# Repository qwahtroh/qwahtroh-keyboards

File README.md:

# qwahtroh-keyboards
my keyboard projects

usually inspired by a cool keyboard on r/mk that wasn't hotswap or ortholinear

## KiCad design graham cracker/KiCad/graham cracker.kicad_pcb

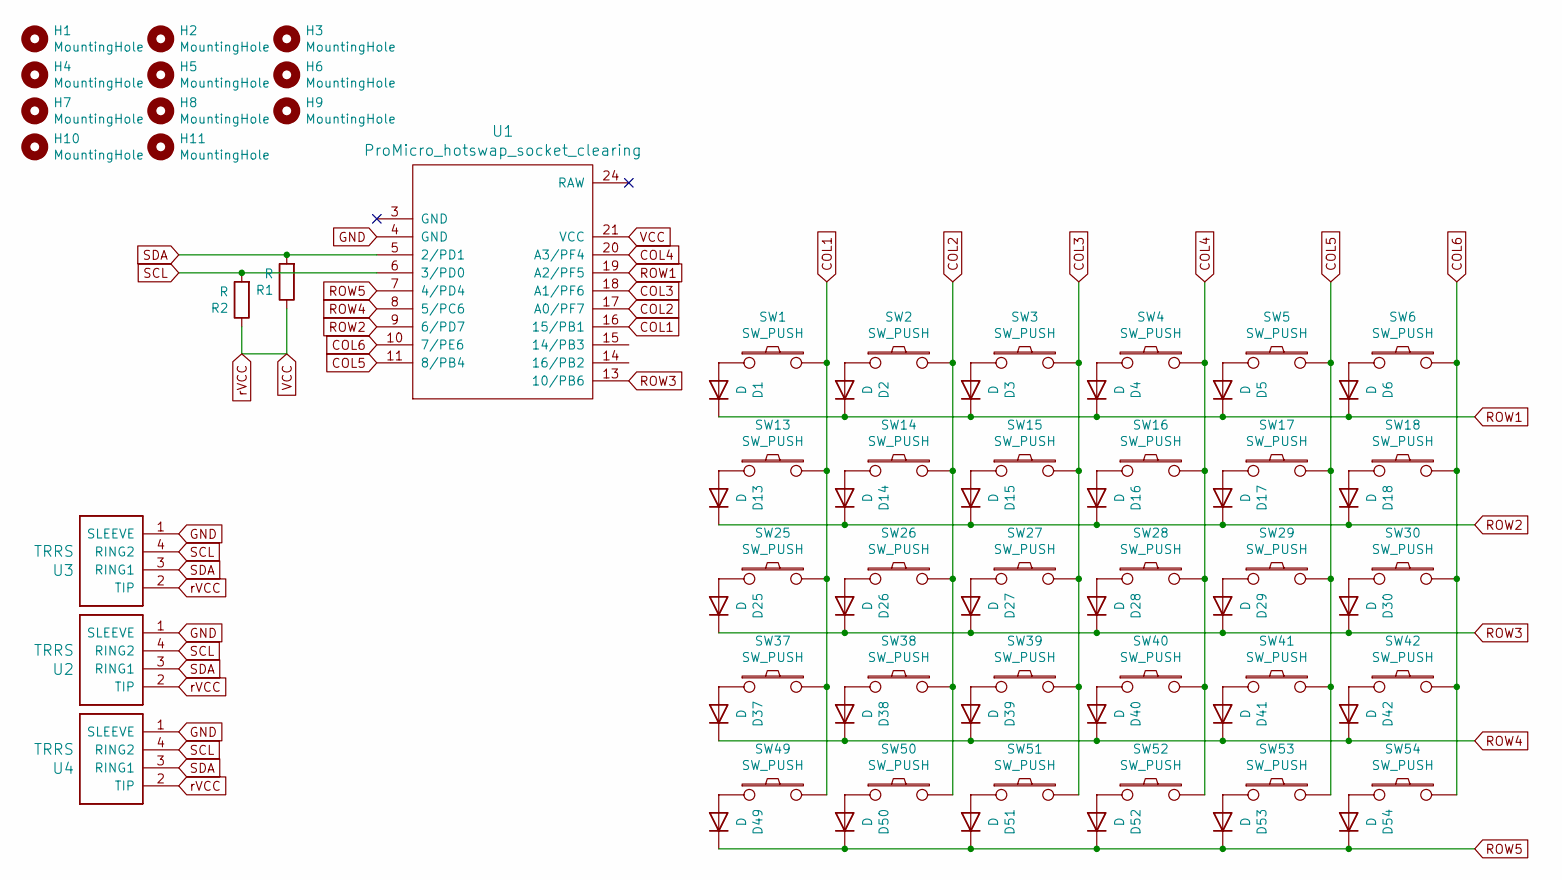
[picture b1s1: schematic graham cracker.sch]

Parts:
D1, D2, D3, D4, D5, D6, D13, D14, D15, D16, D17, D18, D25, D26, D27, D28, D29, D30, D37, D38, D39, D40, D41, D42, D49, D50, D51, D52, D53, D54: D; D_SOD123F
H1, H2, H3, H4, H5, H6, H7, H8, H9, H10, H11: MountingHole; HOLE_M3
R1, R2: R; R_Axial_DIN0207_L6.3mm_D2.5mm_P10.16mm_Horizontal
SW1, SW2, SW3, SW4, SW5, SW6, SW13, SW14, SW15, SW16, SW17, SW18, SW25, SW26, SW27, SW28, SW29, SW30, SW37, SW38, SW39, SW40, SW41, SW42, SW49, SW50, SW51, SW52, SW53, SW54: SW_PUSH; Kailh_MX_Socket
U1: ProMicro_hotswap_socket_clearing; ArduinoProMicro_hotswap_socket_clear
U2, U3, U4: TRRS; TRRS-PJ-320A

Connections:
COL1: SW1.2, SW13.2, SW25.2, SW37.2, SW49.2, U1.16 (15/PB1)
COL2: SW2.2, SW14.2, SW26.2, SW38.2, SW50.2, U1.17 (A0/PF7)
COL3: SW3.2, SW15.2, SW27.2, SW39.2, SW51.2, U1.18 (A1/PF6)
COL4: SW4.2, SW16.2, SW28.2, SW40.2, SW52.2, U1.20 (A3/PF4)
COL5: SW5.2, SW17.2, SW29.2, SW41.2, SW53.2, U1.11 (8/PB4)
COL6: SW6.2, SW18.2, SW30.2, SW42.2, SW54.2, U1.10 (7/PE6)
GND: U1.4 (GND), U2.1 (SLEEVE), U3.1 (SLEEVE), U4.1 (SLEEVE)
unnamed: D1.2 (A), SW1.1
unnamed: D2.2 (A), SW2.1
unnamed: D3.2 (A), SW3.1
unnamed: D4.2 (A), SW4.1
unnamed: D5.2 (A), SW5.1
unnamed: D6.2 (A), SW6.1
unnamed: D13.2 (A), SW13.1
unnamed: D14.2 (A), SW14.1
unnamed: D15.2 (A), SW15.1
unnamed: D16.2 (A), SW16.1
unnamed: D17.2 (A), SW17.1
unnamed: D18.2 (A), SW18.1
unnamed: D25.2 (A), SW25.1
unnamed: D26.2 (A), SW26.1
unnamed: D27.2 (A), SW27.1
unnamed: D28.2 (A), SW28.1
unnamed: D29.2 (A), SW29.1
unnamed: D30.2 (A), SW30.1
unnamed: D37.2 (A), SW37.1
unnamed: D38.2 (A), SW38.1
unnamed: D39.2 (A), SW39.1
unnamed: D40.2 (A), SW40.1
unnamed: D41.2 (A), SW41.1
unnamed: D42.2 (A), SW42.1
unnamed: D49.2 (A), SW49.1
unnamed: D50.2 (A), SW50.1
unnamed: D51.2 (A), SW51.1
unnamed: D52.2 (A), SW52.1
unnamed: D53.2 (A), SW53.1
unnamed: D54.2 (A), SW54.1
ROW1: D1.1 (K), D2.1 (K), D3.1 (K), D4.1 (K), D5.1 (K), D6.1 (K), U1.19 (A2/PF5)
ROW2: D13.1 (K), D14.1 (K), D15.1 (K), D16.1 (K), D17.1 (K), D18.1 (K), U1.9 (6/PD7)
ROW3: D25.1 (K), D26.1 (K), D27.1 (K), D28.1 (K), D29.1 (K), D30.1 (K), U1.13 (10/PB6)
ROW4: D37.1 (K), D38.1 (K), D39.1 (K), D40.1 (K), D41.1 (K), D42.1 (K), U1.8 (5/PC6)
ROW5: D49.1 (K), D50.1 (K), D51.1 (K), D52.1 (K), D53.1 (K), D54.1 (K), U1.7 (4/PD4)
SCL: R2.2, U1.6 (3/PD0), U2.4 (RING2), U3.4 (RING2), U4.4 (RING2)
SDA: R1.2, U1.5 (2/PD1), U2.3 (RING1), U3.3 (RING1), U4.3 (RING1)
VCC: R1.1, R2.1, U1.21 (VCC), U2.2 (TIP), U3.2 (TIP), U4.2 (TIP)

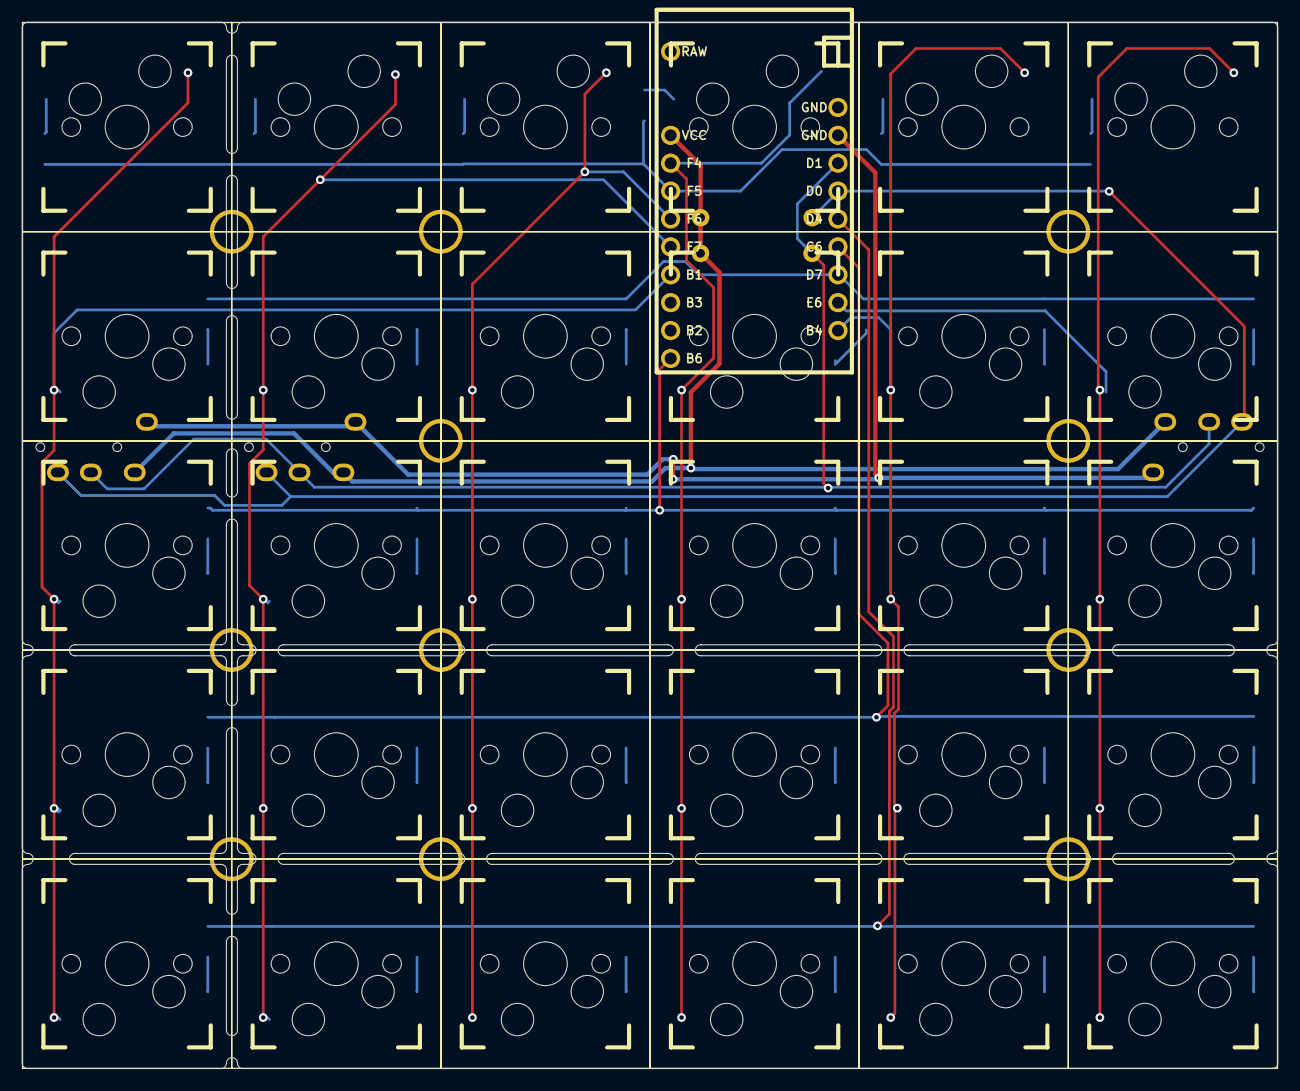
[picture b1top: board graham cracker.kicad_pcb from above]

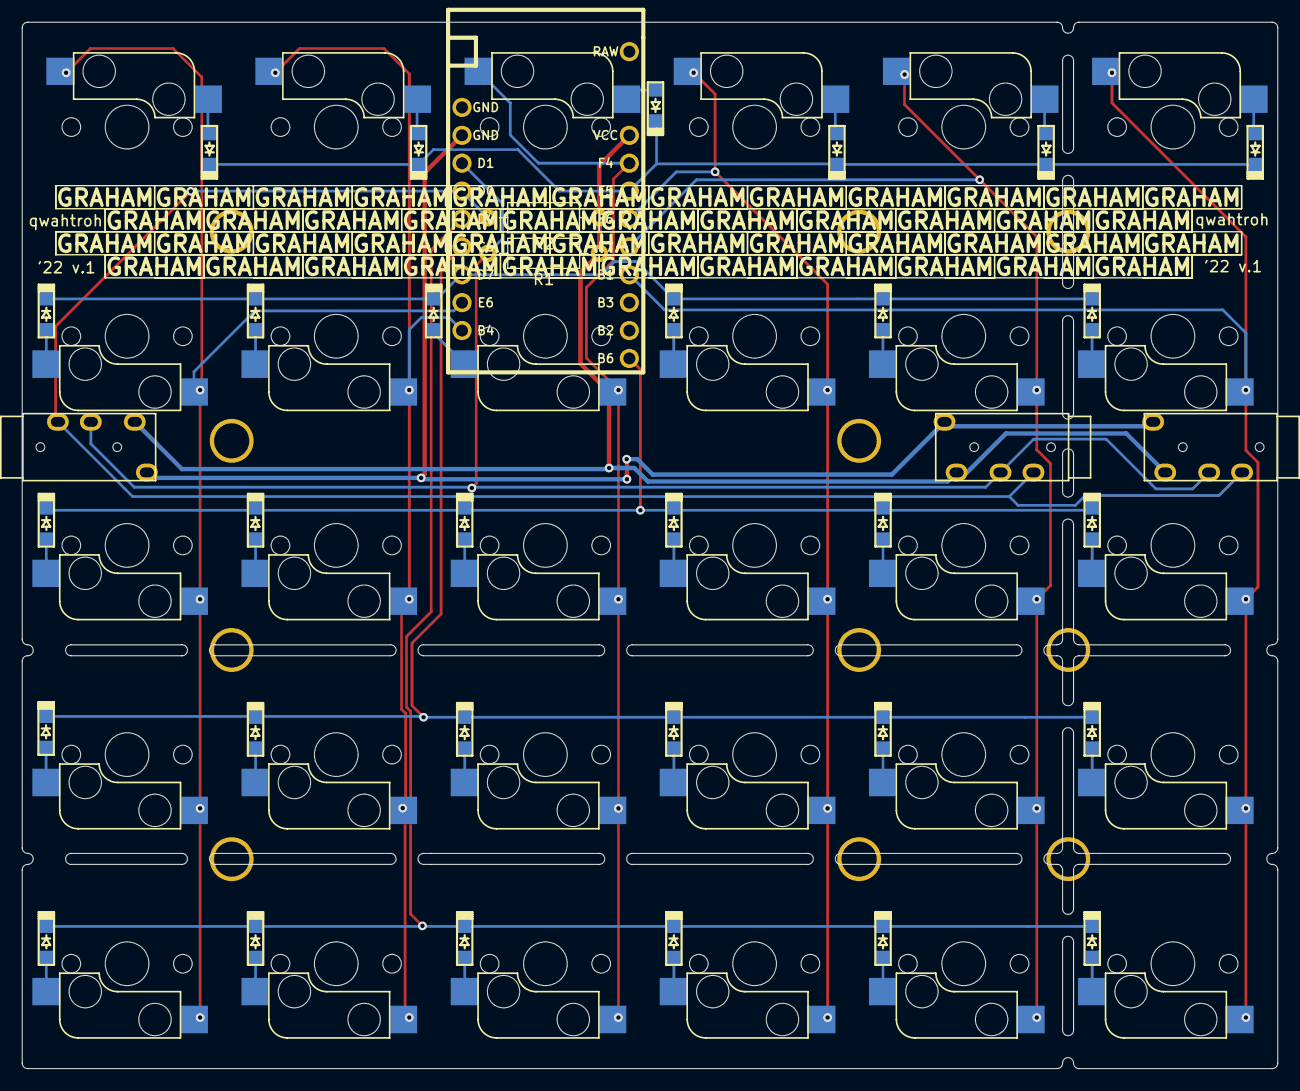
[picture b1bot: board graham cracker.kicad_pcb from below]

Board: 2 copper layers, 114.3 x 95.3 mm, 77 parts (36 on the bottom side), 45 nets.

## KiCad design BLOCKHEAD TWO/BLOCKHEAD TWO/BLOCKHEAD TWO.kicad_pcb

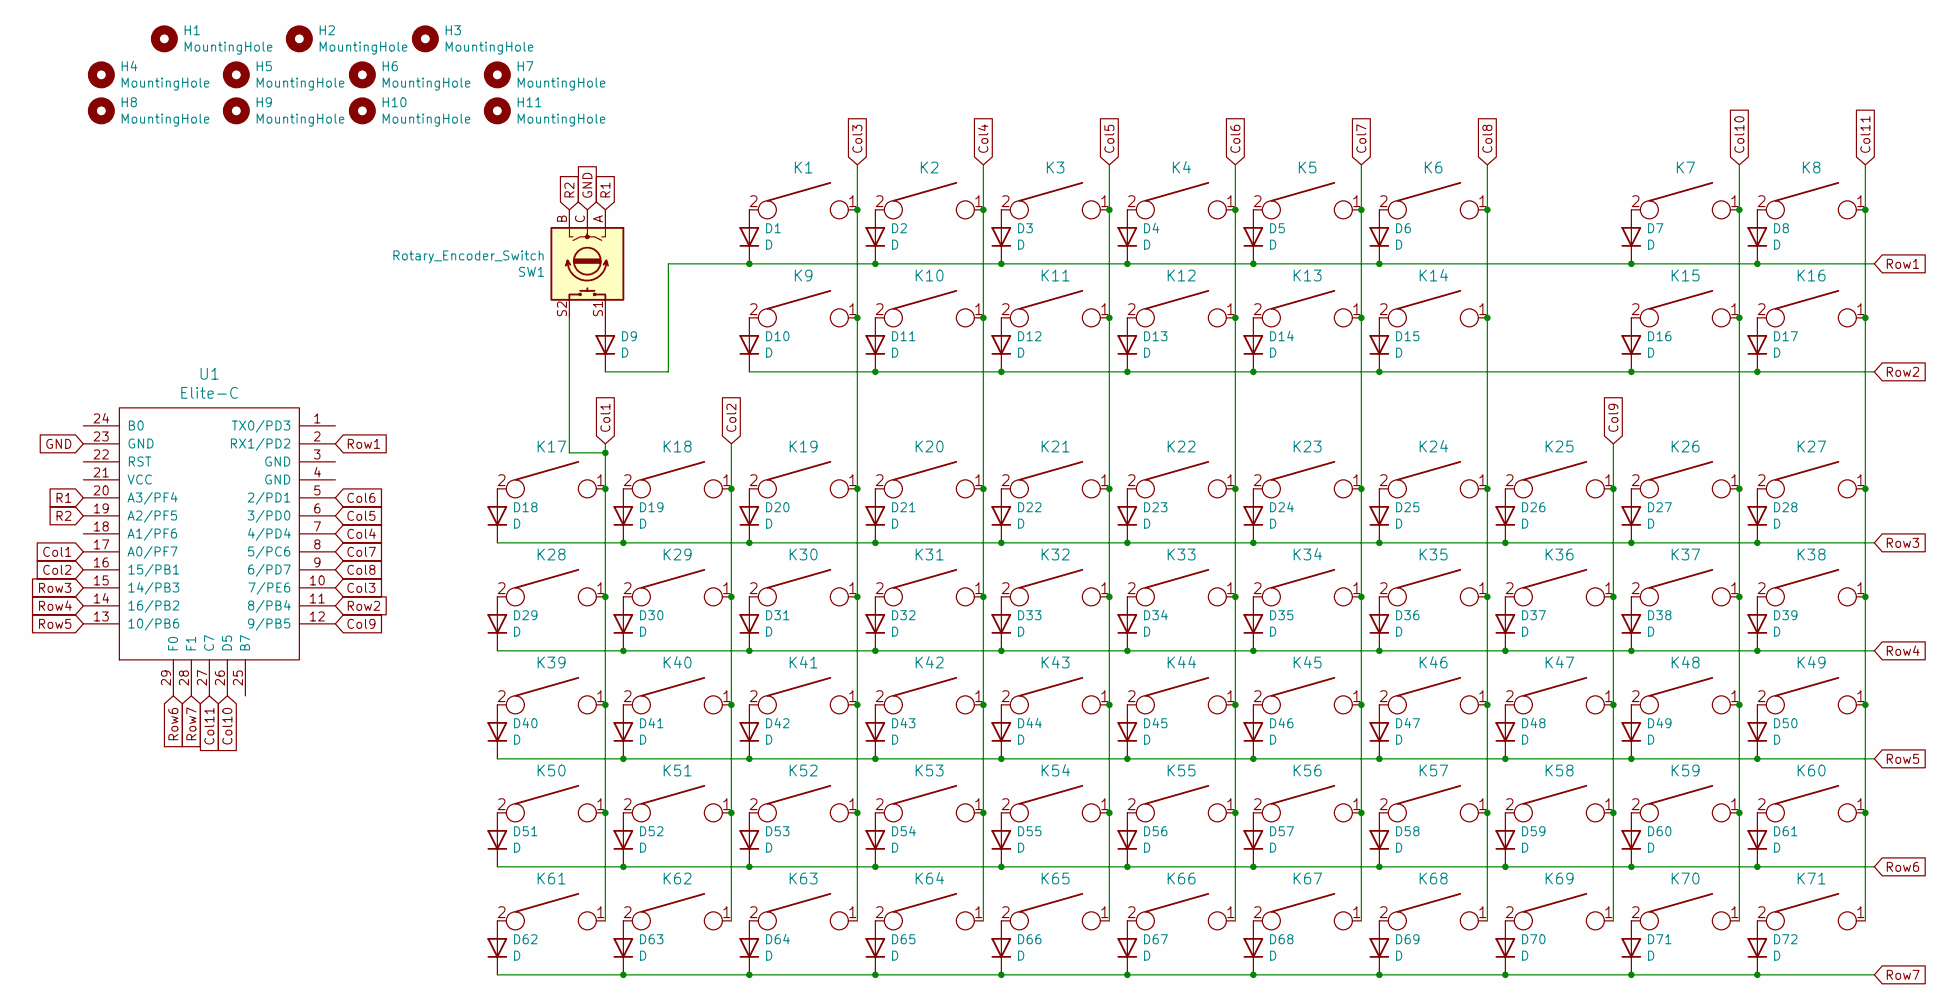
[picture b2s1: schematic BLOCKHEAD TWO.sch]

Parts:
D1, D2, D3, D4, D5, D6, D7, D8, D9, D10, D11, D12, D13, D14, D15, D16, D17, D18, D19, D20, D21, D22, D23, D24, D25, D26, D27, D28, D29, D30, D31, D32, D33, D34, D35, D36, D37, D38, D39, D40, D41, D42, D43, D44, D45, D46, D47, D48, D49, D50, D51, D52, D53, D54, D55, D56, D57, D58, D59, D60, D61, D62, D63, D64, D65, D66, D67, D68, D69, D70, D71, D72: D; D_SOD123F
H1, H2, H3, H4, H5, H6, H7, H8, H9, H10, H11: MountingHole; HOLE_M3
K1, K2, K3, K4, K5, K6, K7, K8, K9, K10, K11, K12, K13, K14, K15, K16, K17, K18, K19, K20, K21, K22, K23, K24, K25, K26, K27, K28, K29, K30, K31, K32, K33, K34, K35, K36, K37, K38, K39, K40, K41, K42, K43, K44, K45, K46, K47, K48, K49, K50, K51, K52, K53, K54, K55, K56, K57, K58, K59, K60, K61, K62, K63, K64, K65, K66, K67, K68, K69, K70, K71: KEYSW; Kailh_MX_Socket
SW1: Rotary_Encoder_Switch; RotaryEncoder_EC11
U1: Elite-C

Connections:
Col1: K17.1, K28.1, K39.1, K50.1, K61.1, SW1.S2, U1.17 (A0/PF7)
Col2: K18.1, K29.1, K40.1, K51.1, K62.1, U1.16 (15/PB1)
Col3: K1.1, K9.1, K19.1, K30.1, K41.1, K52.1, K63.1, U1.10 (7/PE6)
Col4: K2.1, K10.1, K20.1, K31.1, K42.1, K53.1, K64.1, U1.7 (4/PD4)
Col5: K3.1, K11.1, K21.1, K32.1, K43.1, K54.1, K65.1, U1.6 (3/PD0)
Col6: K4.1, K12.1, K22.1, K33.1, K44.1, K55.1, K66.1, U1.5 (2/PD1)
Col7: K5.1, K13.1, K23.1, K34.1, K45.1, K56.1, K67.1, U1.8 (5/PC6)
Col8: K6.1, K14.1, K24.1, K35.1, K46.1, K57.1, K68.1, U1.9 (6/PD7)
Col9: K25.1, K36.1, K47.1, K58.1, K69.1, U1.12 (9/PB5)
Col10: K7.1, K15.1, K26.1, K37.1, K48.1, K59.1, K70.1, U1.26 (D5)
Col11: K8.1, K16.1, K27.1, K38.1, K49.1, K60.1, K71.1, U1.27 (C7)
GND: SW1.C, U1.23 (GND)
unnamed: D1.2 (A), K1.2
unnamed: D2.2 (A), K2.2
unnamed: D3.2 (A), K3.2
unnamed: D4.2 (A), K4.2
unnamed: D5.2 (A), K5.2
unnamed: D6.2 (A), K6.2
unnamed: D7.2 (A), K7.2
unnamed: D8.2 (A), K8.2
unnamed: D9.2 (A), SW1.S1
unnamed: D10.2 (A), K9.2
unnamed: D11.2 (A), K10.2
unnamed: D12.2 (A), K11.2
unnamed: D13.2 (A), K12.2
unnamed: D14.2 (A), K13.2
unnamed: D15.2 (A), K14.2
unnamed: D16.2 (A), K15.2
unnamed: D17.2 (A), K16.2
unnamed: D18.2 (A), K17.2
unnamed: D19.2 (A), K18.2
unnamed: D20.2 (A), K19.2
unnamed: D21.2 (A), K20.2
unnamed: D22.2 (A), K21.2
unnamed: D23.2 (A), K22.2
unnamed: D24.2 (A), K23.2
unnamed: D25.2 (A), K24.2
unnamed: D26.2 (A), K25.2
unnamed: D27.2 (A), K26.2
unnamed: D28.2 (A), K27.2
unnamed: D29.2 (A), K28.2
unnamed: D30.2 (A), K29.2
unnamed: D31.2 (A), K30.2
unnamed: D32.2 (A), K31.2
unnamed: D33.2 (A), K32.2
unnamed: D34.2 (A), K33.2
unnamed: D35.2 (A), K34.2
unnamed: D36.2 (A), K35.2
unnamed: D37.2 (A), K36.2
unnamed: D38.2 (A), K37.2
unnamed: D39.2 (A), K38.2
unnamed: D40.2 (A), K39.2
unnamed: D41.2 (A), K40.2
unnamed: D42.2 (A), K41.2
unnamed: D43.2 (A), K42.2
unnamed: D44.2 (A), K43.2
unnamed: D45.2 (A), K44.2
unnamed: D46.2 (A), K45.2
unnamed: D47.2 (A), K46.2
unnamed: D48.2 (A), K47.2
unnamed: D49.2 (A), K48.2
unnamed: D50.2 (A), K49.2
unnamed: D51.2 (A), K50.2
unnamed: D52.2 (A), K51.2
unnamed: D53.2 (A), K52.2
unnamed: D54.2 (A), K53.2
unnamed: D55.2 (A), K54.2
unnamed: D56.2 (A), K55.2
unnamed: D57.2 (A), K56.2
unnamed: D58.2 (A), K57.2
unnamed: D59.2 (A), K58.2
unnamed: D60.2 (A), K59.2
unnamed: D61.2 (A), K60.2
unnamed: D62.2 (A), K61.2
unnamed: D63.2 (A), K62.2
unnamed: D64.2 (A), K63.2
unnamed: D65.2 (A), K64.2
unnamed: D66.2 (A), K65.2
unnamed: D67.2 (A), K66.2
unnamed: D68.2 (A), K67.2
unnamed: D69.2 (A), K68.2
unnamed: D70.2 (A), K69.2
unnamed: D71.2 (A), K70.2
unnamed: D72.2 (A), K71.2
R1: SW1.A, U1.20 (A3/PF4)
R2: SW1.B, U1.19 (A2/PF5)
Row1: D1.1 (K), D2.1 (K), D3.1 (K), D4.1 (K), D5.1 (K), D6.1 (K), D7.1 (K), D8.1 (K), D9.1 (K), U1.2 (RX1/PD2)
Row2: D10.1 (K), D11.1 (K), D12.1 (K), D13.1 (K), D14.1 (K), D15.1 (K), D16.1 (K), D17.1 (K), U1.11 (8/PB4)
Row3: D18.1 (K), D19.1 (K), D20.1 (K), D21.1 (K), D22.1 (K), D23.1 (K), D24.1 (K), D25.1 (K), D26.1 (K), D27.1 (K), D28.1 (K), U1.15 (14/PB3)
Row4: D29.1 (K), D30.1 (K), D31.1 (K), D32.1 (K), D33.1 (K), D34.1 (K), D35.1 (K), D36.1 (K), D37.1 (K), D38.1 (K), D39.1 (K), U1.14 (16/PB2)
Row5: D40.1 (K), D41.1 (K), D42.1 (K), D43.1 (K), D44.1 (K), D45.1 (K), D46.1 (K), D47.1 (K), D48.1 (K), D49.1 (K), D50.1 (K), U1.13 (10/PB6)
Row6: D51.1 (K), D52.1 (K), D53.1 (K), D54.1 (K), D55.1 (K), D56.1 (K), D57.1 (K), D58.1 (K), D59.1 (K), D60.1 (K), D61.1 (K), U1.29 (F0)
Row7: D62.1 (K), D63.1 (K), D64.1 (K), D65.1 (K), D66.1 (K), D67.1 (K), D68.1 (K), D69.1 (K), D70.1 (K), D71.1 (K), D72.1 (K), U1.28 (F1)

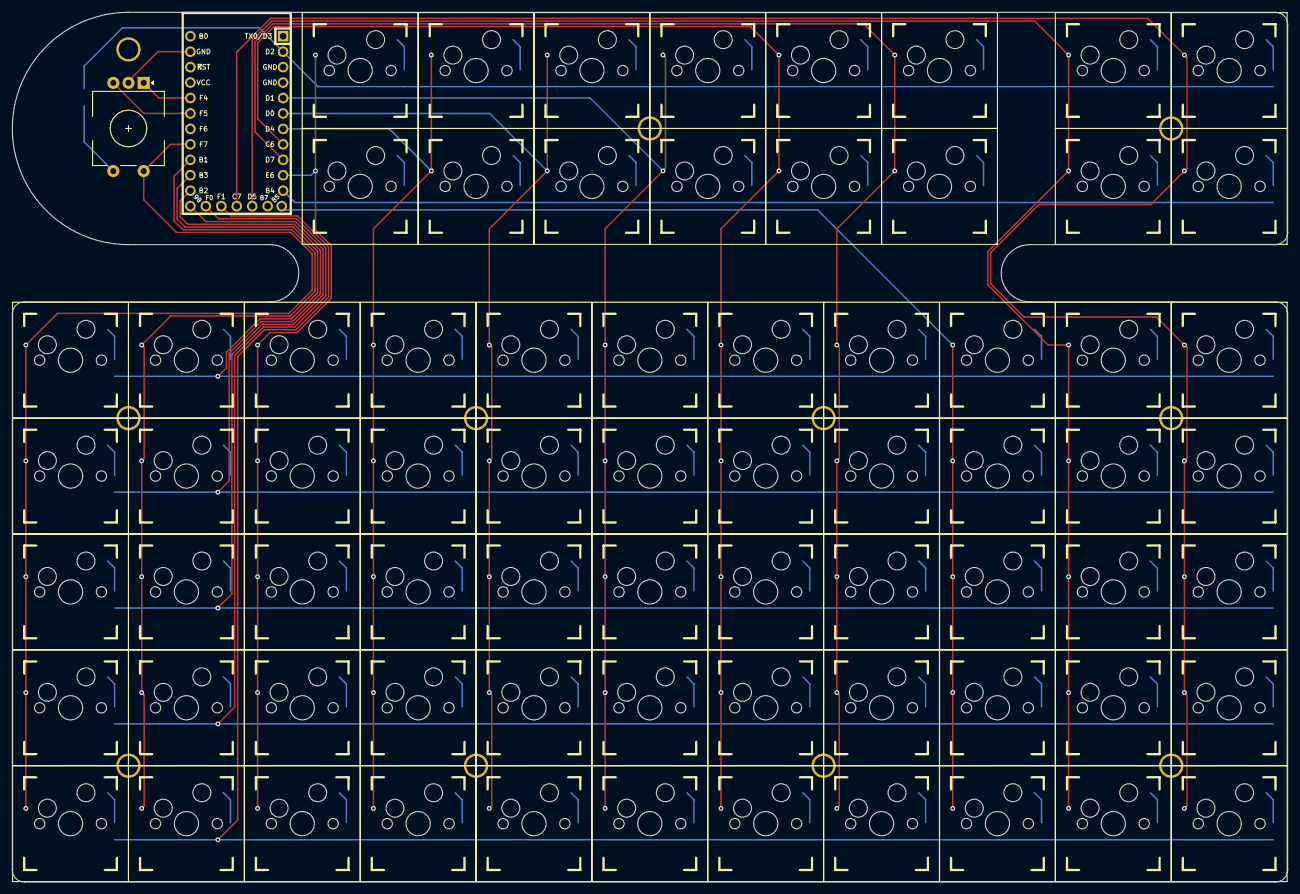
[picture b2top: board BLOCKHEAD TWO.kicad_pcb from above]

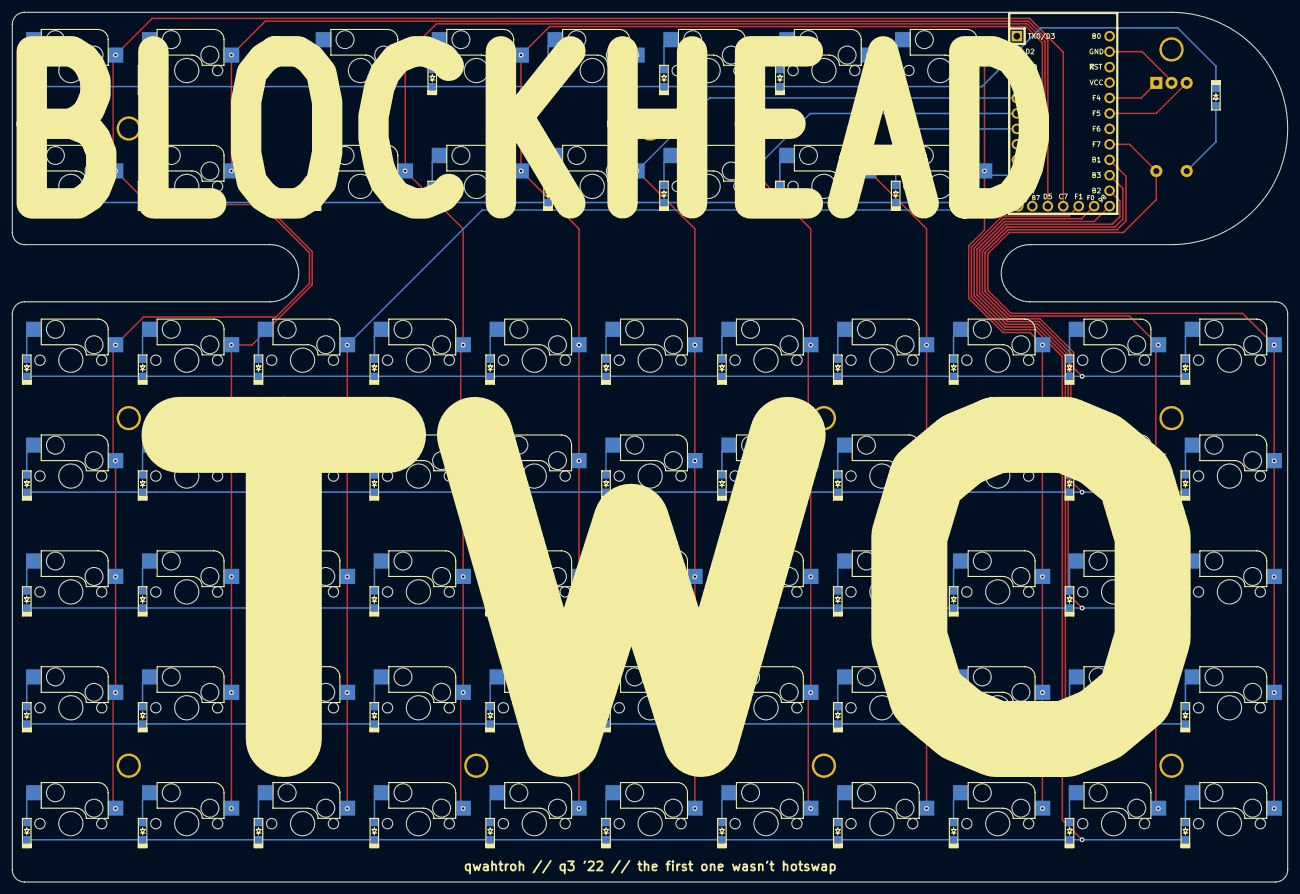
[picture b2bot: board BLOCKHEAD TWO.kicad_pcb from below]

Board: 2 copper layers, 209.7 x 143.0 mm, 156 parts (73 on the bottom side), 93 nets.

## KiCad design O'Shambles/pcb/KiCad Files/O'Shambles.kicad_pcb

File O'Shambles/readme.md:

# DTM

Copyright <2020> <Armand Grant> <armand.grant.2000@gmail.com> @<qwahtroh>

This program is free software: you can redistribute it and/or modify
it under the terms of the GNU General Public License as published by
the Free Software Foundation, either version 2 of the License, or
(at your option) any later version.

This program is distributed in the hope that it will be useful,
but WITHOUT ANY WARRANTY; without even the implied warranty of
MERCHANTABILITY or FITNESS FOR A PARTICULAR PURPOSE.  See the
GNU General Public License for more details.

You should have received a copy of the GNU General Public License
along with this program.  If not, see <http://www.gnu.org/license

===

A 4x11 (+6) keyboard with two rotary encoders. No modifiers on the outermost columns. Instead, there's an extra column in the middle. Hence dTm - Down The Middle

Keyboard Maintainer: Armand G / qwahtroh
Hardware Supported: Proton C
Hardware Availability: Handwired

Make example for this keyboard (after setting up your build environment)
    
    make qwahtroh/DTM:default

See the [build environment setup](https://docs.qmk.fm/#/getting_started_build_tools) and the [make instructions](https://docs.qmk.fm/#/getting_started_make_guide) for more information. Brand new to QMK? Start with our [Complete Newbs Guide](https://docs.qmk.fm/#/newbs).

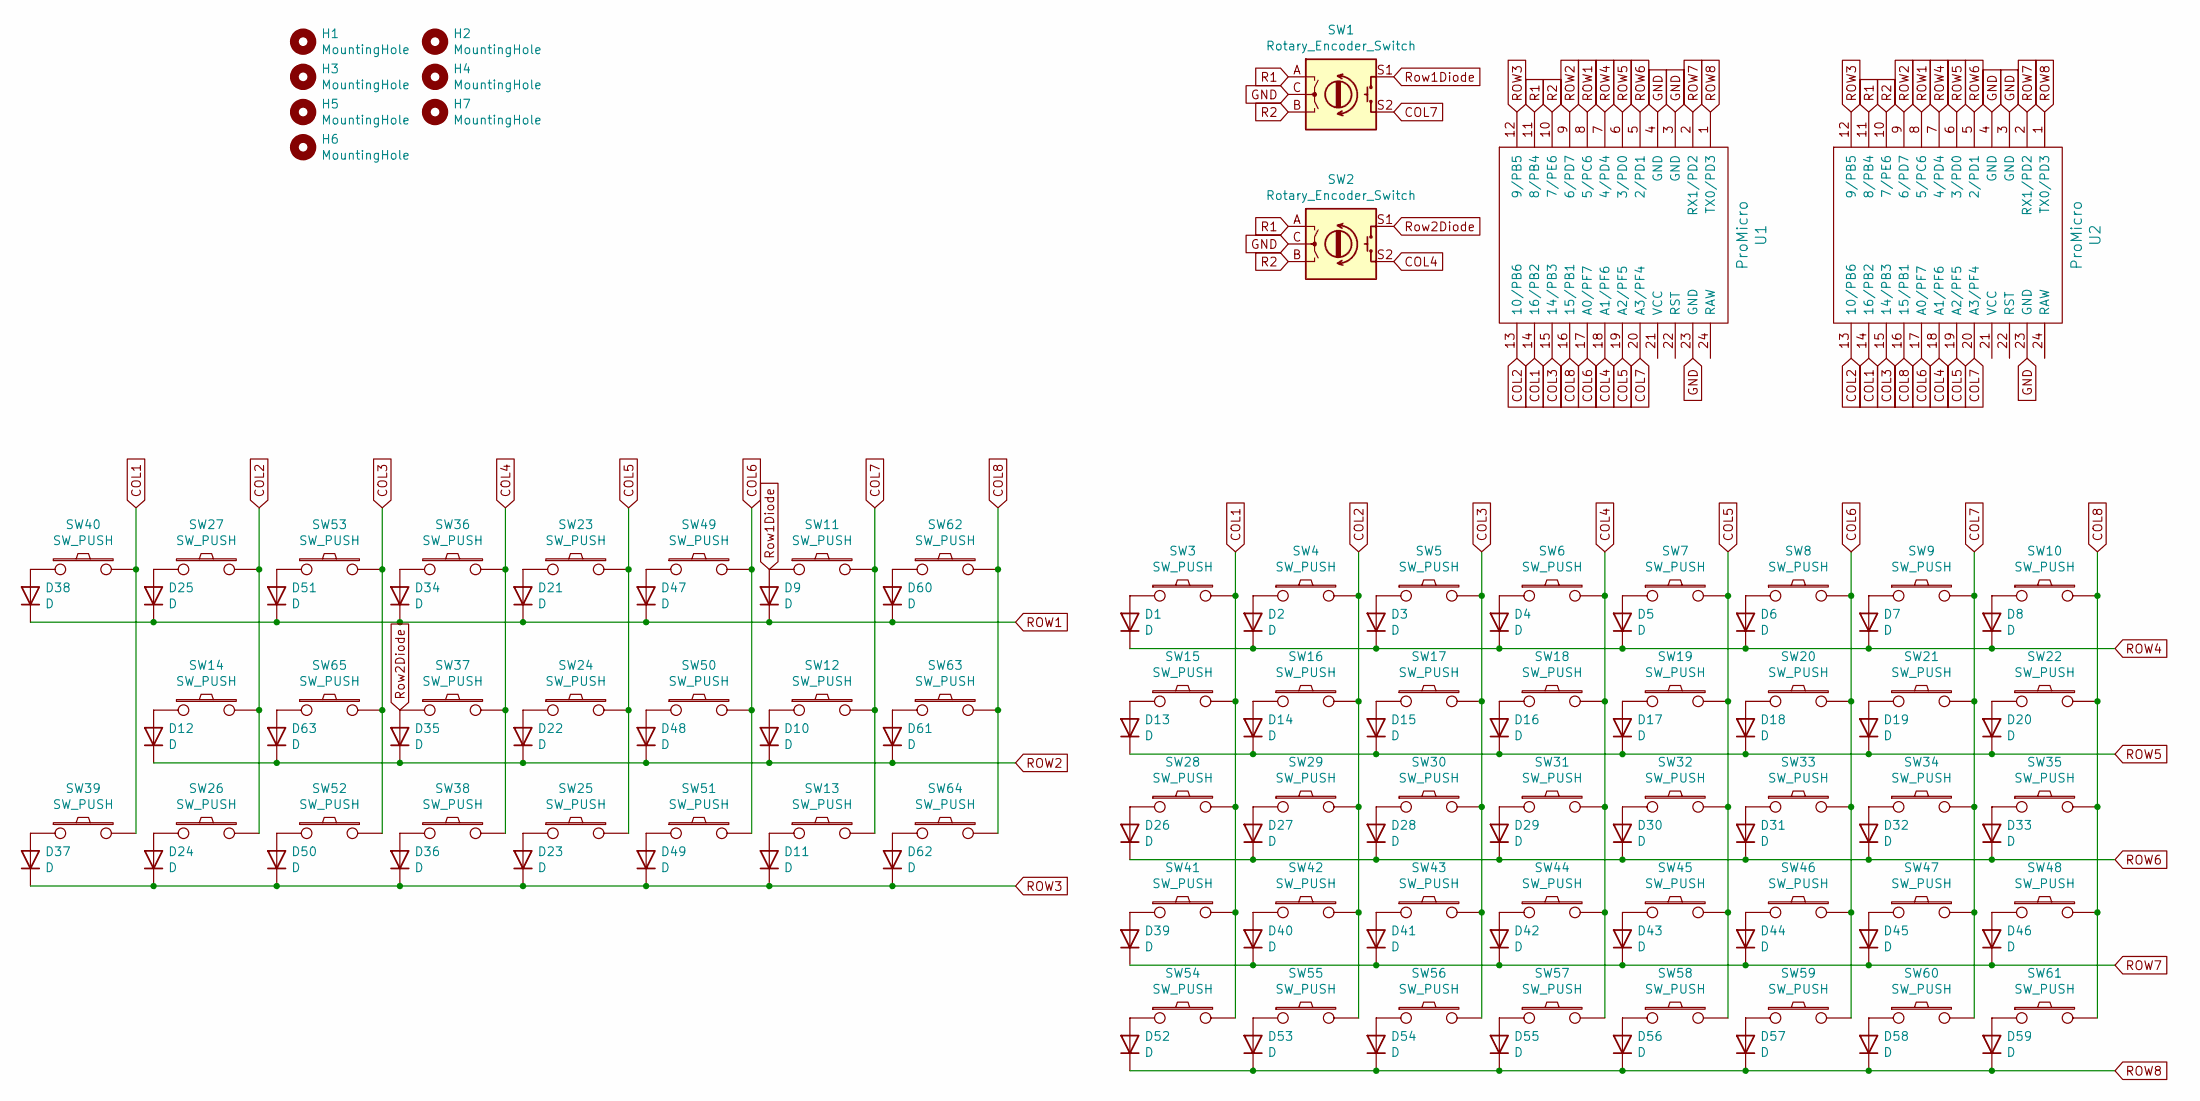
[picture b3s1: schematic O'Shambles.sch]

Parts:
D1, D2, D3, D4, D5, D6, D7, D8, D9, D10, D11, D12, D13, D14, D15, D16, D17, D18, D19, D20, D21, D22, D23, D24, D25, D26, D27, D28, D29, D30, D31, D32, D33, D34, D35, D36, D37, D38, D39, D40, D41, D42, D43, D44, D45, D46, D47, D48, D49, D50, D51, D52, D53, D54, D55, D56, D57, D58, D59, D60, D61, D62, D63: D; D_SOD123F
H1, H2, H3, H4, H5, H6, H7: MountingHole; HOLE_M3
SW1, SW2: Rotary_Encoder_Switch; RotaryEncoder_EC11
SW3, SW4, SW5, SW6, SW7, SW8, SW9, SW10, SW11, SW12, SW13, SW14, SW15, SW16, SW17, SW18, SW19, SW20, SW21, SW22, SW23, SW24, SW25, SW26, SW27, SW28, SW29, SW30, SW31, SW32, SW33, SW34, SW35, SW36, SW37, SW38, SW39, SW40, SW41, SW42, SW43, SW44, SW45, SW46, SW47, SW48, SW49, SW50, SW51, SW52, SW53, SW54, SW55, SW56, SW57, SW58, SW59, SW60, SW61, SW62, SW63, SW64, SW65: SW_PUSH; Kailh_MX_Socket_reversible
U1, U2: ProMicro; ArduinoProMicro

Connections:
COL1: SW3.2, SW15.2, SW28.2, SW39.2, SW40.2, SW41.2, SW54.2, U1.14 (16/PB2), U2.14 (16/PB2)
COL2: SW4.2, SW14.2, SW16.2, SW26.2, SW27.2, SW29.2, SW42.2, SW55.2, U1.13 (10/PB6), U2.13 (10/PB6)
COL3: SW5.2, SW17.2, SW30.2, SW43.2, SW52.2, SW53.2, SW56.2, SW65.2, U1.15 (14/PB3), U2.15 (14/PB3)
COL4: SW2.S2, SW6.2, SW18.2, SW31.2, SW36.2, SW37.2, SW38.2, SW44.2, SW57.2, U1.18 (A1/PF6), U2.18 (A1/PF6)
COL5: SW7.2, SW19.2, SW23.2, SW24.2, SW25.2, SW32.2, SW45.2, SW58.2, U1.19 (A2/PF5), U2.19 (A2/PF5)
COL6: SW8.2, SW20.2, SW33.2, SW46.2, SW49.2, SW50.2, SW51.2, SW59.2, U1.17 (A0/PF7), U2.17 (A0/PF7)
COL7: SW1.S2, SW9.2, SW11.2, SW12.2, SW13.2, SW21.2, SW34.2, SW47.2, SW60.2, U1.20 (A3/PF4), U2.20 (A3/PF4)
COL8: SW10.2, SW22.2, SW35.2, SW48.2, SW61.2, SW62.2, SW63.2, SW64.2, U1.16 (15/PB1), U2.16 (15/PB1)
GND: SW1.C, SW2.C, U1.3 (GND), U1.4 (GND), U1.23 (GND), U2.3 (GND), U2.4 (GND), U2.23 (GND)
unnamed: D1.2 (A), SW3.1
unnamed: D2.2 (A), SW4.1
unnamed: D3.2 (A), SW5.1
unnamed: D4.2 (A), SW6.1
unnamed: D5.2 (A), SW7.1
unnamed: D6.2 (A), SW8.1
unnamed: D7.2 (A), SW9.1
unnamed: D8.2 (A), SW10.1
unnamed: D10.2 (A), SW12.1
unnamed: D11.2 (A), SW13.1
unnamed: D12.2 (A), SW14.1
unnamed: D13.2 (A), SW15.1
unnamed: D14.2 (A), SW16.1
unnamed: D15.2 (A), SW17.1
unnamed: D16.2 (A), SW18.1
unnamed: D17.2 (A), SW19.1
unnamed: D18.2 (A), SW20.1
unnamed: D19.2 (A), SW21.1
unnamed: D20.2 (A), SW22.1
unnamed: D21.2 (A), SW23.1
unnamed: D22.2 (A), SW24.1
unnamed: D23.2 (A), SW25.1
unnamed: D24.2 (A), SW26.1
unnamed: D25.2 (A), SW27.1
unnamed: D26.2 (A), SW28.1
unnamed: D27.2 (A), SW29.1
unnamed: D28.2 (A), SW30.1
unnamed: D29.2 (A), SW31.1
unnamed: D30.2 (A), SW32.1
unnamed: D31.2 (A), SW33.1
unnamed: D32.2 (A), SW34.1
unnamed: D33.2 (A), SW35.1
unnamed: D34.2 (A), SW36.1
unnamed: D36.2 (A), SW38.1
unnamed: D37.2 (A), SW39.1
unnamed: D38.2 (A), SW40.1
unnamed: D39.2 (A), SW41.1
unnamed: D40.2 (A), SW42.1
unnamed: D41.2 (A), SW43.1
unnamed: D42.2 (A), SW44.1
unnamed: D43.2 (A), SW45.1
unnamed: D44.2 (A), SW46.1
unnamed: D45.2 (A), SW47.1
unnamed: D46.2 (A), SW48.1
unnamed: D47.2 (A), SW49.1
unnamed: D48.2 (A), SW50.1
unnamed: D49.2 (A), SW51.1
unnamed: D50.2 (A), SW52.1
unnamed: D51.2 (A), SW53.1
unnamed: D52.2 (A), SW54.1
unnamed: D53.2 (A), SW55.1
unnamed: D54.2 (A), SW56.1
unnamed: D55.2 (A), SW57.1
unnamed: D56.2 (A), SW58.1
unnamed: D57.2 (A), SW59.1
unnamed: D58.2 (A), SW60.1
unnamed: D59.2 (A), SW61.1
unnamed: D60.2 (A), SW62.1
unnamed: D61.2 (A), SW63.1
unnamed: D62.2 (A), SW64.1
unnamed: D63.2 (A), SW65.1
R1: SW1.A, SW2.A, U1.11 (8/PB4), U2.11 (8/PB4)
R2: SW1.B, SW2.B, U1.10 (7/PE6), U2.10 (7/PE6)
ROW1: D9.1 (K), D21.1 (K), D25.1 (K), D34.1 (K), D38.1 (K), D47.1 (K), D51.1 (K), D60.1 (K), U1.8 (5/PC6), U2.8 (5/PC6)
ROW2: D10.1 (K), D12.1 (K), D22.1 (K), D35.1 (K), D48.1 (K), D61.1 (K), D63.1 (K), U1.9 (6/PD7), U2.9 (6/PD7)
ROW3: D11.1 (K), D23.1 (K), D24.1 (K), D36.1 (K), D37.1 (K), D49.1 (K), D50.1 (K), D62.1 (K), U1.12 (9/PB5), U2.12 (9/PB5)
ROW4: D1.1 (K), D2.1 (K), D3.1 (K), D4.1 (K), D5.1 (K), D6.1 (K), D7.1 (K), D8.1 (K), U1.7 (4/PD4), U2.7 (4/PD4)
ROW5: D13.1 (K), D14.1 (K), D15.1 (K), D16.1 (K), D17.1 (K), D18.1 (K), D19.1 (K), D20.1 (K), U1.6 (3/PD0), U2.6 (3/PD0)
ROW6: D26.1 (K), D27.1 (K), D28.1 (K), D29.1 (K), D30.1 (K), D31.1 (K), D32.1 (K), D33.1 (K), U1.5 (2/PD1), U2.5 (2/PD1)
ROW7: D39.1 (K), D40.1 (K), D41.1 (K), D42.1 (K), D43.1 (K), D44.1 (K), D45.1 (K), D46.1 (K), U1.2 (RX1/PD2), U2.2 (RX1/PD2)
ROW8: D52.1 (K), D53.1 (K), D54.1 (K), D55.1 (K), D56.1 (K), D57.1 (K), D58.1 (K), D59.1 (K), U1.1 (TX0/PD3), U2.1 (TX0/PD3)
Row1Diode: D9.2 (A), SW1.S1, SW11.1
Row2Diode: D35.2 (A), SW2.S1, SW37.1

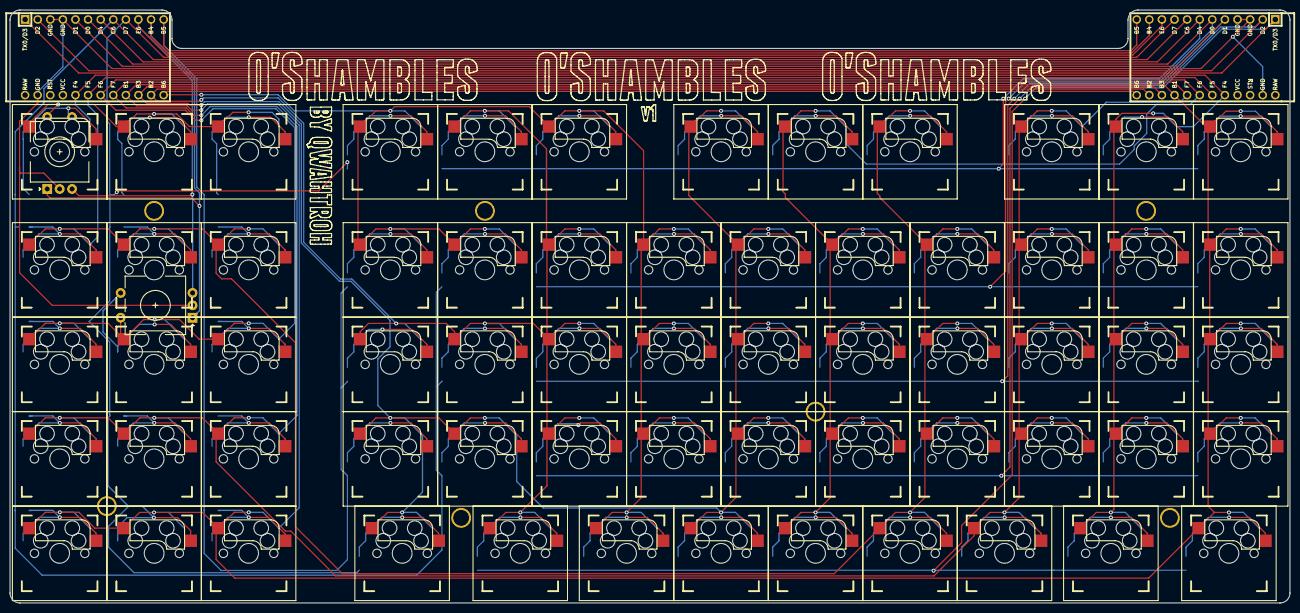
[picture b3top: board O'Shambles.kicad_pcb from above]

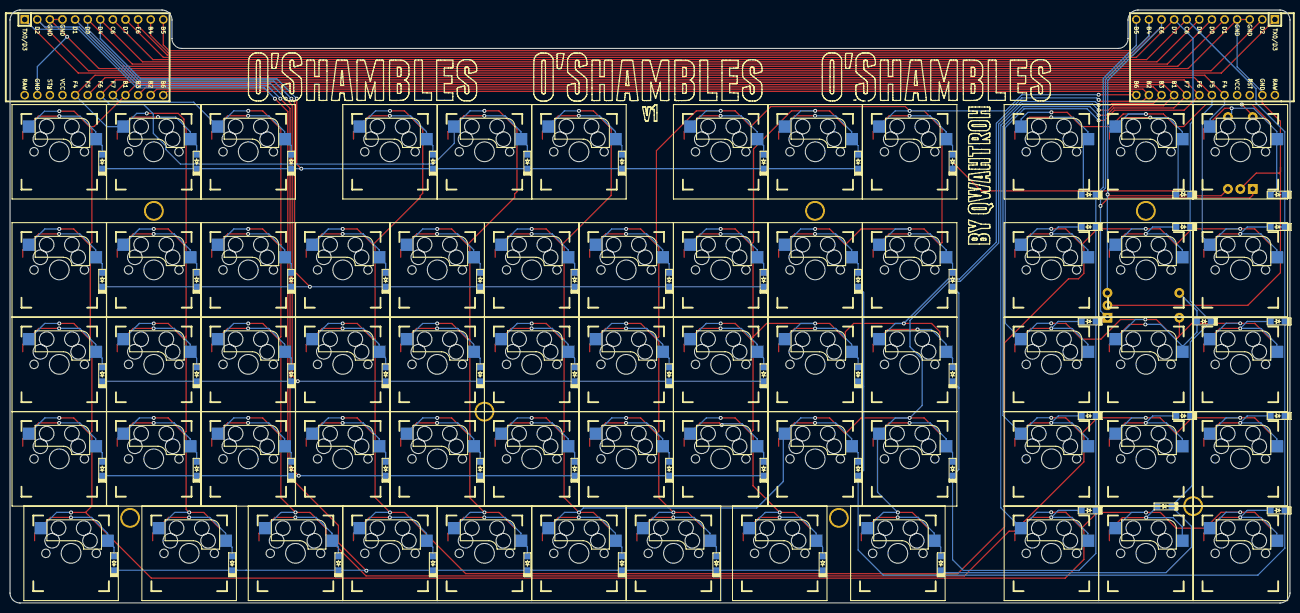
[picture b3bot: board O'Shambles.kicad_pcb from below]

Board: 2 copper layers, 258.1 x 119.5 mm, 137 parts (64 on the bottom side), 82 nets.

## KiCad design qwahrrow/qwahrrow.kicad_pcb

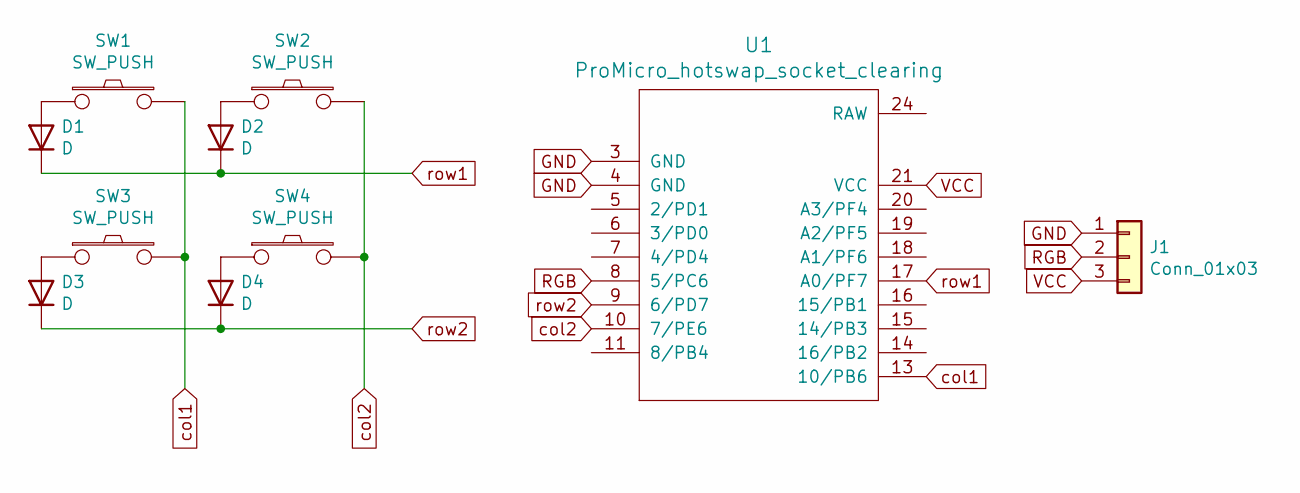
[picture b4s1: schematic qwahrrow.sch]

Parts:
D1, D2, D3, D4: D; D_SOD123
J1: Conn_01x03; PinHeader_1x03_P2.54mm_Vertical
SW1, SW2, SW3, SW4: SW_PUSH; Kailh_MX_Socket
U1: ProMicro_hotswap_socket_clearing; ArduinoProMicro_hotswap_socket_clear

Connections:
GND: J1.1, U1.3 (GND), U1.4 (GND)
unnamed: D1.2 (A), SW1.1
unnamed: D2.2 (A), SW2.1
unnamed: D3.2 (A), SW3.1
unnamed: D4.2 (A), SW4.1
RGB: J1.2, U1.8 (5/PC6)
VCC: J1.3, U1.21 (VCC)
col1: SW1.2, SW3.2, U1.13 (10/PB6)
col2: SW2.2, SW4.2, U1.10 (7/PE6)
row1: D1.1 (K), D2.1 (K), U1.17 (A0/PF7)
row2: D3.1 (K), D4.1 (K), U1.9 (6/PD7)

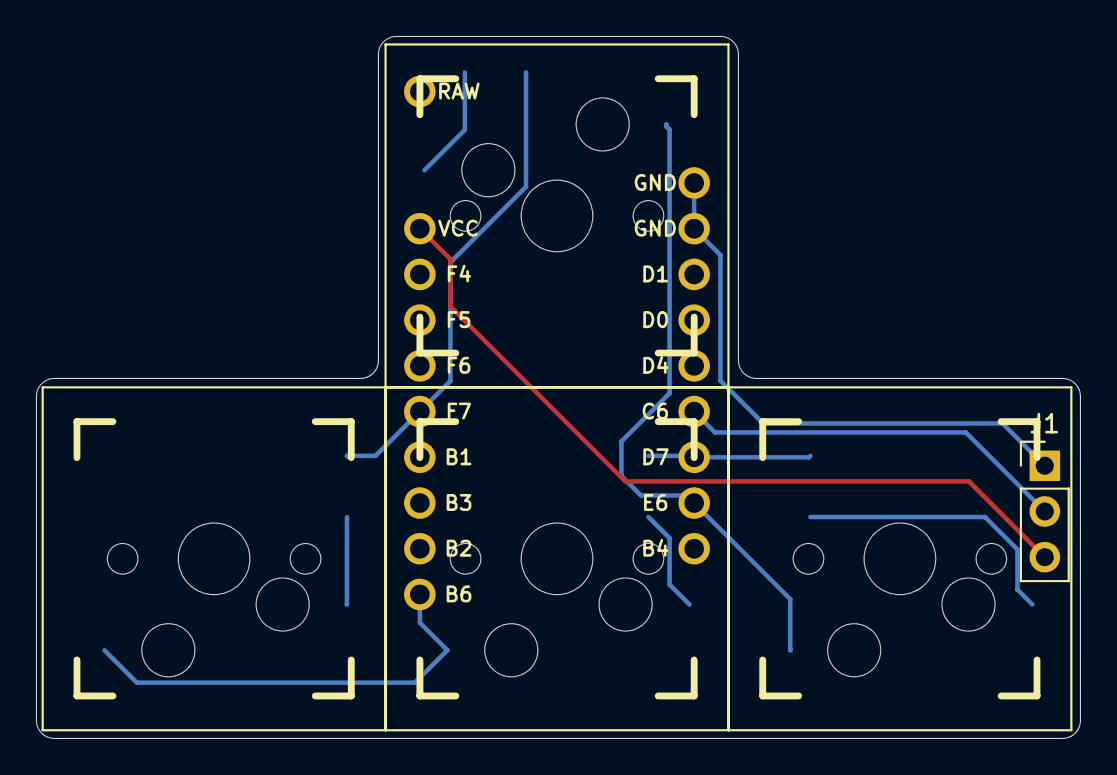
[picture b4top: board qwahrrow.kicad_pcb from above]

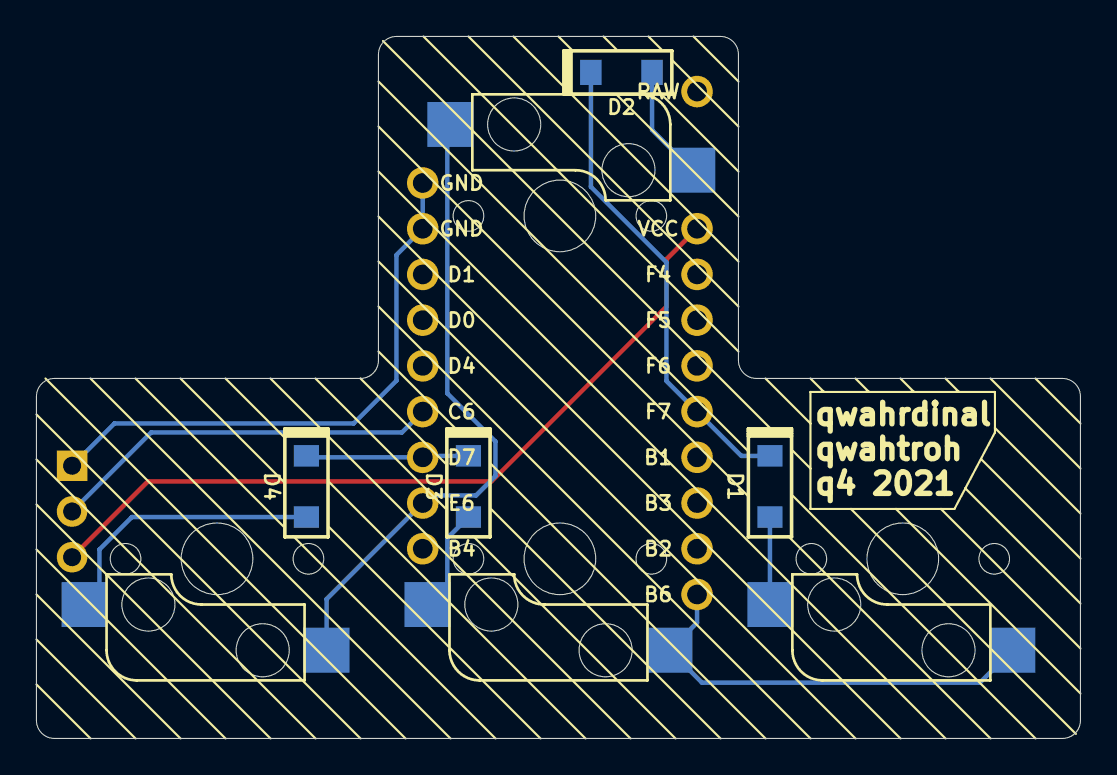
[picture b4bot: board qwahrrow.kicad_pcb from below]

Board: 2 copper layers, 58.0 x 39.0 mm, 10 parts (5 on the bottom side), 11 nets.
